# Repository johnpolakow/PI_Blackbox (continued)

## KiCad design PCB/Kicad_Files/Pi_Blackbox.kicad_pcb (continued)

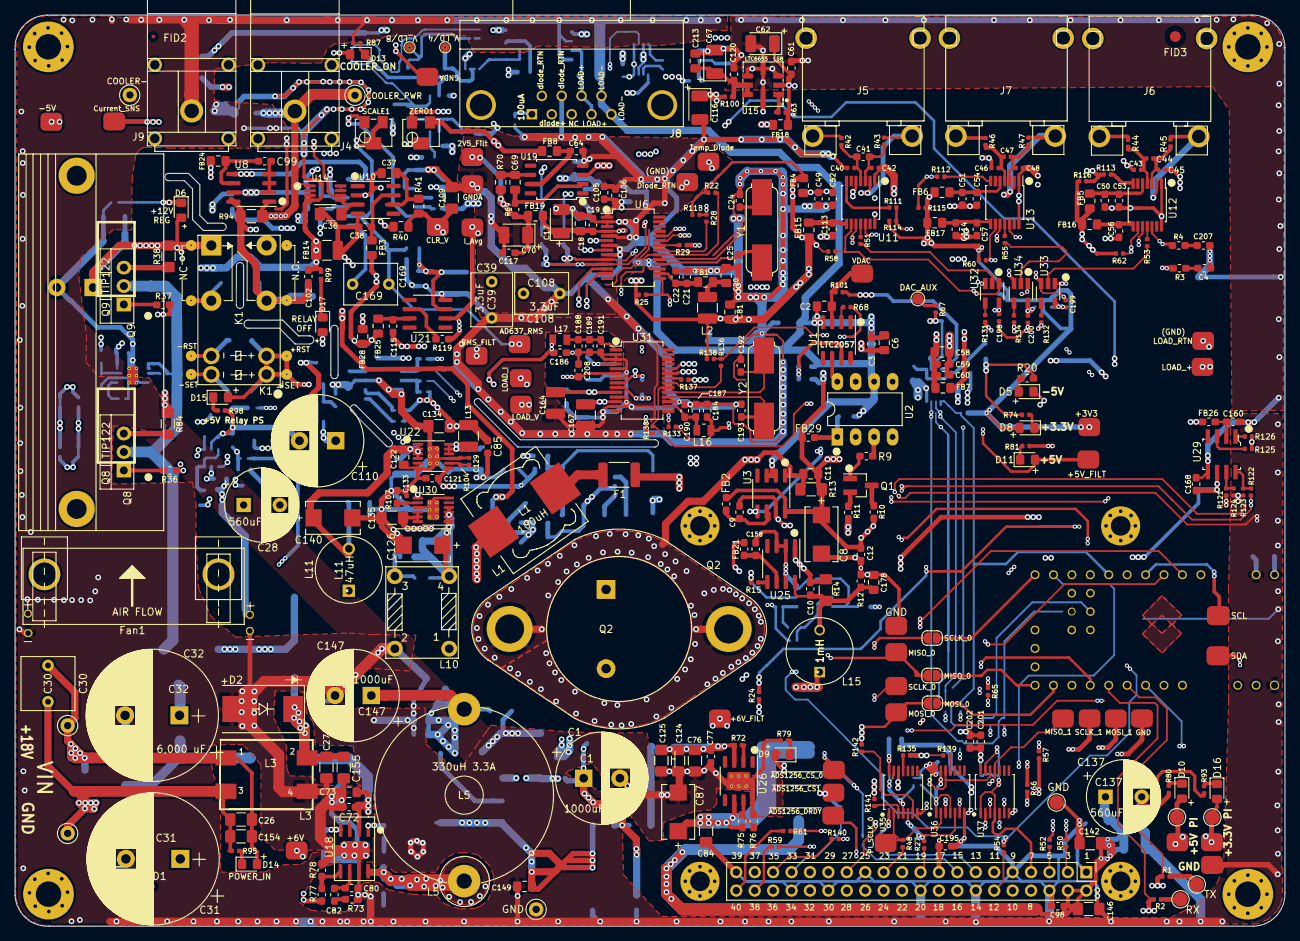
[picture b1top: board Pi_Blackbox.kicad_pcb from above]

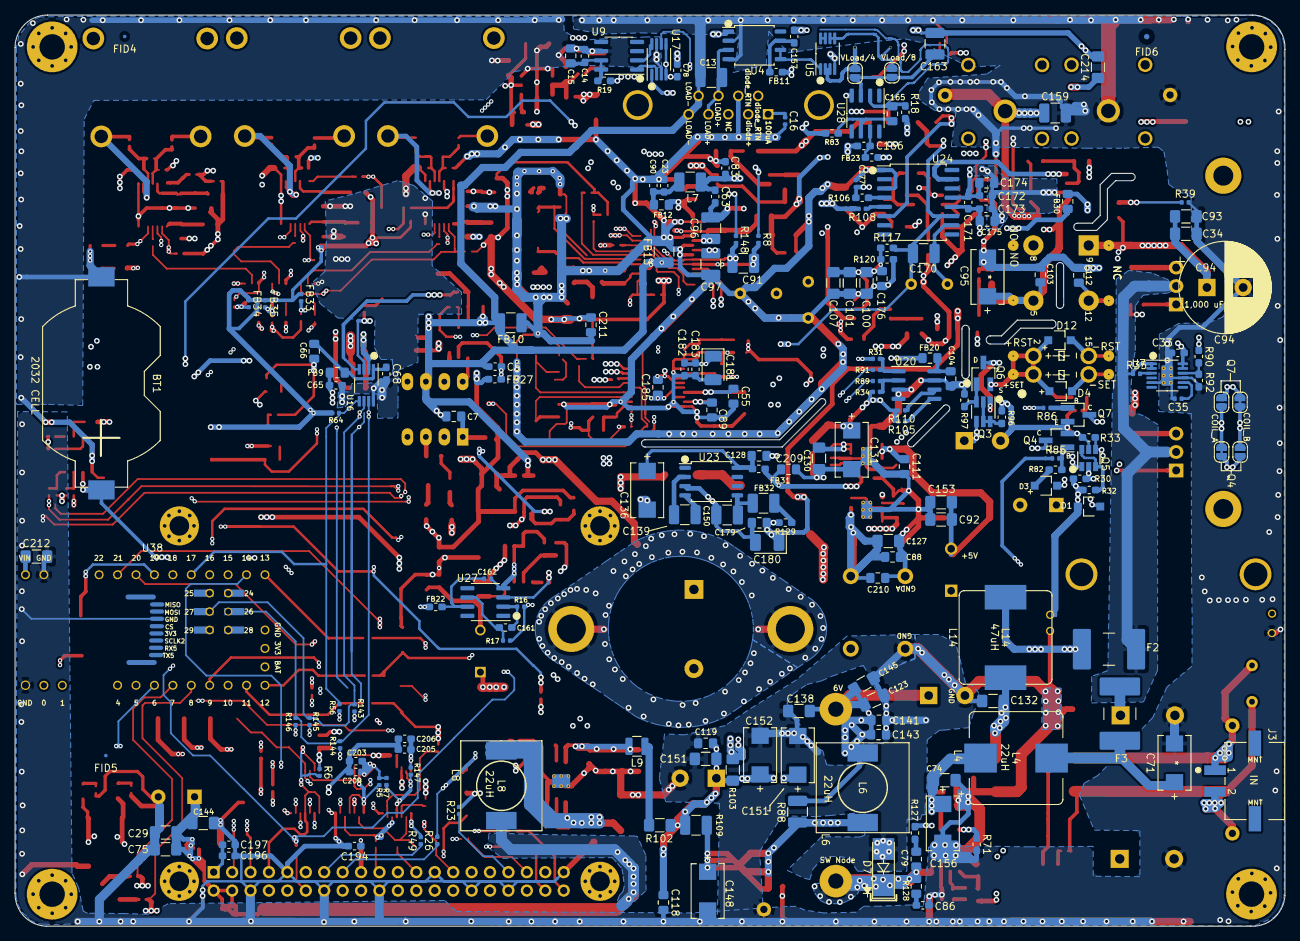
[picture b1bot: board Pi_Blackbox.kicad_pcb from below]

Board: 6 copper layers, 175.1 x 125.6 mm, 569 parts (201 on the bottom side), 276 nets.

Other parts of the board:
C151#2: 4.7uF; C_1206_3216Metric_Pad1.42x1.75mm_HandSolder
C212: 10uF; C_1206_3216Metric_Pad1.42x1.75mm_HandSolder
JP5: MOSI_0; SolderJumper-2_P1.3mm_Open_RoundedPad1.0x1.5mm
JP6: MISO_0; SolderJumper-2_P1.3mm_Open_RoundedPad1.0x1.5mm
JP7: SCLK_0; SolderJumper-2_P1.3mm_Open_RoundedPad1.0x1.5mm
U38: Teensy4.0_min_pads; Teensy40_most_pads_small_holes

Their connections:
+6V: C151#2.1; also elsewhere on the board
ADS1256_MISO: JP6.1; also elsewhere on the board
ADS1256_MOSI: JP5.1; also elsewhere on the board
ADS1256_SCLK: JP7.1; also elsewhere on the board
DAC8552_CS: U38.17; also elsewhere on the board
DAC_MOSI: U38.26; also elsewhere on the board
DAC_SCLK: U38.27; also elsewhere on the board
GND: C151#2.2, C212.2, U38.GND; also elsewhere on the board
MAX31856_CS_1: U38.4; also elsewhere on the board
MAX31856_CS_2: U38.5; also elsewhere on the board
MAX31856_CS_3: U38.20; also elsewhere on the board
MAX31856_DRDY_1: U38.21; also elsewhere on the board
MAX31856_DRDY_2: U38.28; also elsewhere on the board
MAX31856_DRDY_3: U38.29; also elsewhere on the board
MAX31856_MISO: U38.1; also elsewhere on the board
unnamed: JP5.2, U38.11
unnamed: JP6.2, U38.12
unnamed: JP7.2, U38.13
PI_+5V: C212.1, U38.VIN; also elsewhere on the board
PI_SCL: U38.19; also elsewhere on the board
PI_SDA: U38.18; also elsewhere on the board
PI_UART_RX: U38.8; also elsewhere on the board
PI_UART_TX: U38.7; also elsewhere on the board
VBat: U38.VBAT; also elsewhere on the board
~ADS1256_CS_0: U38.10; also elsewhere on the board
~ADS1256_CS_1: U38.0; also elsewhere on the board
~ADS1256_RESET: U38.22; also elsewhere on the board
~ADS1265_DRDY: U38.6; also elsewhere on the board
~ADS1265_DRDY2: U38.9; also elsewhere on the board
~BUF_EN_0: U38.14; also elsewhere on the board
~BUF_EN_1: U38.15; also elsewhere on the board
~BUF_EN_2: U38.16; also elsewhere on the board

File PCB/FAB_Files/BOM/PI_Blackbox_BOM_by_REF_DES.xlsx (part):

| Ref | Value | Description | Footprint | MFR | MFR PN | Digikey PN | Price EA
 | C2 | 1uF | 1uF, 50V, X7R | 0805 | AVX |  | 478-7956-1-ND | 0.35
 | C3 | .1uF | 50V Ceramic Capacitor X7R 0603 | 0603 | Samsung |  | 1276-1000-1-ND | 0.1
 | C5 | .1uF | 50V Ceramic Capacitor X7R 0603 | 0603 | Samsung |  | 1276-1000-1-ND | 0.1
 | C6 | 1uF | CAP CER 1UF 25V X7R 0805 | 0805 |  |  | 399-8004-1-ND | 0.15
 | C7 | 1uF | CAP CER 1UF 25V X7R 0805 | 0805 |  |  | 399-8004-1-ND | 0.15
 | C8 | 47uF | CAP TANT 47UF 10% 35V 2917 T495X | T495X476K035ATE300 | Kemet |  | 399-3905-1-ND | 2.41
 | C9 | .1uF | 50V Ceramic Capacitor X7R 0603 | 0603 | Samsung |  | 1276-1000-1-ND | 0.1
 | C10 | .1uF | 50V Ceramic Capacitor X7R 0603 | 0603 | Samsung |  | 1276-1000-1-ND | 0.1
 | C11 | .1uF | 50V Ceramic Capacitor X7R 0603 | 0603 | Samsung |  | 1276-1000-1-ND | 0.1
 | C12 | .1uF | 50V Ceramic Capacitor X7R 0603 | 0603 | Samsung |  | 1276-1000-1-ND | 0.1
 | C13 | 1uF | 1uF Film 16VDC | 1210 |  |  | 338-2778-1-ND | 0.94
 | C14 | .1uF | 50V Ceramic Capacitor X7R 0603 | 0603 | Samsung |  | 1276-1000-1-ND | 0.1
 | C15 | 1uF | CAP CER 1UF 25V X7R 0805 | 0805 |  |  | 399-8004-1-ND | 0.15
 | C16 | 1000pF | CAP CER 1000PF 16V X7R 0402 | 0402 | Kemet |  | 399-1032-1-ND | 0.1
 | C17 | 4.7uF | CAP TANT 4.7UF 10% 35V 1411 | Tantalum_3528-21_Kemet-B_Pad | Kemet |  | 399-10431-1-ND | 0.95
 | C18 | 1uF | CAP CER 1UF 25V X7R 0805 | 0805 |  |  | 399-8004-1-ND | 0.15
 | C19 | .1uF | 50V Ceramic Capacitor X7R 0603 | 0603 | Samsung |  | 1276-1000-1-ND | 0.1
 | C20 | 1uF | CAP CER 1UF 25V X7R 0805 | 0805 |  |  | 399-8004-1-ND | 0.15
 | C21 | .1uF | 50V Ceramic Capacitor X7R 0603 | 0603 | Samsung |  | 1276-1000-1-ND | 0.1
 | C22 | .1uF | 50V Ceramic Capacitor X7R 0603 | 0603 | Samsung |  | 1276-1000-1-ND | 0.1
 | C23 | 1uF | CAP CER 1UF 25V X7R 0603 | 0603 | Kemet |  | 399-7376-1-ND | 0.3
 | C24 | 20pF | 20pF, 50V, C0G | 0603 | Murata |  | 490-1410-1-ND | 0.1
 | C25 | 20pF | 20pF, 50V, C0G | 0603 | Murata |  | 490-1410-1-ND | 0.1
 | C26 | .1uF | CAP CER 0.1UF 50V Z5U 1206 | 1206 | Kemet | C1206C104Z5UACTU | 399-1258-1-ND | 0.19
 | C27 | .01uF | CAP CER 10000PF 50V X7R 1206 | 1206 | Yageo | CC1206KRX7R9BB103 | 311-1174-1-ND | 0.24
 | C29 | 10uF | CAP CER 10UF 50V X7R 1206 | 1206 | Samsung |  | 1276-6767-1-ND | 0.4
 | C33 | .01uF | 0603 .01UF 10% 50V X7R | 0603 | Kemet |  | 399-C0603C103K5RAC7081CT-ND | 0.11
 | C34 | 10uF | CAP CER 10UF 50V X7R 1206 | 1206 | Samsung |  | 1276-6767-1-ND | 0.4
 | C35 | 1000pF | CAP CER 1000PF 16V X7R 0402 | 0402 | Kemet |  | 399-1032-1-ND | 0.1
 | C36 | 10uF | CAP CER 10UF 50V X7R 1206 | 1206 | Samsung |  | 1276-6767-1-ND | 0.4
 | C37 | 10uF | CAP CER 10UF 16V X7R 0805 | 0805 | Samsung |  | 1276-6472-1-ND | 0.3
 | C38 | .1uF | 50V Ceramic Capacitor X7R 0603 | 0603 | Samsung |  | 1276-1000-1-ND | 0.1
 | C40 | .01uF | C0402C103M5RACTU | 0402 | Kemet |  | 399-7760-1-ND | 0.1
 | C41 | .1uF | 50V Ceramic Capacitor X7R 0603 | 0603 | Samsung |  | 1276-1000-1-ND | 0.1
 | C42 | .01uF | C0402C103M5RACTU | 0402 | Kemet |  | 399-7760-1-ND | 0.1
 | C43 | .01uF | C0402C103M5RACTU | 0402 | Kemet |  | 399-7760-1-ND | 0.1
 | C44 | .1uF | CAP CER 0.1UF 25V X7R 0402 | 0402 | Murata |  | 490-13341-1-ND | 0.1
 | C45 | .01uF | C0402C103M5RACTU | 0402 | Kemet |  | 399-7760-1-ND | 0.1
 | C46 | .01uF | C0402C103M5RACTU | 0402 | Kemet |  | 399-7760-1-ND | 0.1
 | C47 | .1uF | CAP CER 0.1UF 25V X7R 0402 | 0402 | Murata |  | 490-13341-1-ND | 0.1
 | C48 | .01uF | C0402C103M5RACTU | 0402 | Kemet |  | 399-7760-1-ND | 0.1
 | C49 | 1uF | CAP CER 1UF 25V X7R 0805 | 0805 |  |  | 399-8004-1-ND | 0.15
 | C50 | 1uF | CAP CER 1UF 25V X7R 0805 | 0805 |  |  | 399-8004-1-ND | 0.15
 | C51 | 1uF | CAP CER 1UF 25V X7R 0805 | 0805 |  |  | 399-8004-1-ND | 0.15
 | C52 | .1uF | 50V Ceramic Capacitor X7R 0603 | 0603 | Samsung |  | 1276-1000-1-ND | 0.1
 | C53 | .1uF | 50V Ceramic Capacitor X7R 0603 | 0603 | Samsung |  | 1276-1000-1-ND | 0.1
 | C54 | .1uF | 50V Ceramic Capacitor X7R 0603 | 0603 | Samsung |  | 1276-1000-1-ND | 0.1
 | C55 | 1uF | CAP CER 1UF 25V X7R 0805 | 0805 |  |  | 399-8004-1-ND | 0.15
 | C56 | .1uF | 50V Ceramic Capacitor X7R 0603 | 0603 | Samsung |  | 1276-1000-1-ND | 0.1
 | C57 | .1uF | 50V Ceramic Capacitor X7R 0603 | 0603 | Samsung |  | 1276-1000-1-ND | 0.1
 | C58 | 1uF | CAP CER 1UF 25V X7R 0805 | 0805 |  |  | 399-8004-1-ND | 0.15
 | C59 | .1uF | 50V Ceramic Capacitor X7R 0603 | 0603 | Samsung |  | 1276-1000-1-ND | 0.1
 | C60 | .01uF | 0603 .01UF 10% 50V X7R | 0603 | Kemet |  | 399-C0603C103K5RAC7081CT-ND | 0.11
 | C61 | .1uF | 50V Ceramic Capacitor X7R 0603 | 0603 | Samsung |  | 1276-1000-1-ND | 0.1
 | C62 | 4.7uF | CAP TANT 4.7UF 10% 35V 1411 | Tantalum_EIA-3528-21_Kemet-B_Pad | Kemet |  | 399-10431-1-ND | 0.95
 | C63 | .01uF | 0603 .01UF 10% 50V X7R | 0603 | Kemet |  | 399-C0603C103K5RAC7081CT-ND | 0.11
 | C64 | .1uF | 50V Ceramic Capacitor X7R 0603 | 0603 | Samsung |  | 1276-1000-1-ND | 0.1
 | C65 | .01uF | 0603 .01UF 10% 50V X7R | 0603 | Kemet |  | 399-C0603C103K5RAC7081CT-ND | 0.11
 | C66 | 1uF | CAP CER 1UF 25V X7R 0805 | 0805 |  |  | 399-8004-1-ND | 0.15
 | C67 | 4.7uF | CAP TANT 4.7UF 10% 35V 1411 | Tantalum_EIA-3528-21_Kemet-B_Pad | Kemet |  | 399-10431-1-ND | 0.95
 | C68 | .1uF | 50V Ceramic Capacitor X7R 0603 | 0603 | Samsung |  | 1276-1000-1-ND | 0.1
 | C69 | 1uF | CAP CER 1UF 25V X7R 0805 | 0805 |  |  | 399-8004-1-ND | 0.15
 | C70 | 4.7uF | CAP TANT 4.7UF 10% 35V 1411 | Tantalum_EIA-3528-21_Kemet-B_Pad | Kemet |  | 399-10431-1-ND | 0.95
 | C71 | 47uF | CAP TANT 47UF 10% 35V 2917 T495X | T495X476K035ATE300 | Kemet |  | 399-3905-1-ND | 2.41
 | C72 | .1uF | 50V Ceramic Capacitor X7R 0603 | 0603 | Samsung |  | 1276-1000-1-ND | 0.1
 | C73 | 1uF | CAP CER 1UF 25V X7R 0805 | 0805 |  |  | 399-8004-1-ND | 0.15
 | C74 | 10uF | CAP CER 10UF 50V X7R 1206 | 1206 | Samsung |  | 1276-6767-1-ND | 0.4
 | C75 | 10uF | CAP CER 10UF 50V X7R 1206 | 1206 | Samsung |  | 1276-6767-1-ND | 0.4
 | C76 | 10uF | CAP CER 10UF 50V X7R 1206 | 1206 | Samsung |  | 1276-6767-1-ND | 0.4
 | C77 | .1uF | 50V Ceramic Capacitor X7R 0603 | 0603 | Samsung |  | 1276-1000-1-ND | 0.1
 | C78 | .1uF | 50V Ceramic Capacitor X7R 0603 | 0603 | Samsung |  | 1276-1000-1-ND | 0.1
 | C79 | .1uF | CAP CER 0.1UF 25V X7R 0805 | 0805 | Kemet | C0805C104M3RACTU | 399-8000-1-ND | 0.1
 | C80 | 12pF | CAP CER 12PF 50V C0G/NP0 0603 | 0603 | Kemet | C0603C120J5GACTU | 399-1050-1-ND | 0.1
 | C81 | 1uF | CAP CER 1UF 25V X7R 0805 | 0805 |  |  | 399-8004-1-ND | 0.15
 | C82 | 3nF | CAP CER 3000PF 50V C0G/NP0 0603 | 0603 | Murata | GRM1885C1H302JA01D | 490-6384-1-ND | 0.19
 | C83 | .1uF | 50V Ceramic Capacitor X7R 0603 | 0603 | Samsung |  | 1276-1000-1-ND | 0.1
 | C84 | 10uF | CAP CER 10UF 50V X7R 1206 | 1206 | Samsung |  | 1276-6767-1-ND | 0.4
 | C85 | .1uF | 50V Ceramic Capacitor X7R 0603 | 0603 | Samsung |  | 1276-1000-1-ND | 0.1
 | C86 | 680pF | CAP CER 680PF 250V C0G/NP0 0603 | 0603 | Kemet | C0603C681JAGAC7867 | 399-14994-1-ND | 0.11
 | C87 | 47uF | CAP TANT 47UF 10% 35V 2917 T495X | T495X476K035ATE300 | Kemet |  | 399-3905-1-ND | 2.41
 | C88 | 1uF | CAP CER 1UF 25V X7R 0805 | 0805 |  |  | 399-8004-1-ND | 0.15
 | C89 | 1uF | CAP CER 1UF 25V X7R 0805 | 0805 |  |  | 399-8004-1-ND | 0.15
 | C90 | .1uF | 50V Ceramic Capacitor X7R 0603 | 0603 | Samsung |  | 1276-1000-1-ND | 0.1
 | C91 | 1uF | 1uF Film 16VDC | 1210 |  |  | 338-2778-1-ND | 0.94
 | C92 | 10uF | CAP CER 10UF 50V X7R 1206 | 1206 | Samsung |  | 1276-6767-1-ND | 0.4
 | C93 | 10uF | CAP CER 10UF 50V X7R 1206 | 1206 | Samsung |  | 1276-6767-1-ND | 0.4
 | C95 | 47uF | CAP TANT 47UF 10% 35V 2917 T495X | T495X476K035ATE300 | Kemet |  | 399-3905-1-ND | 2.41
 | C96 | 1uF | 1uF Film 16VDC | 1210 |  |  | 338-2778-1-ND | 0.94
 | C97 | 1uF | 1uF Film 16VDC | 1210 |  |  | 338-2778-1-ND | 0.94
 | C98 | 1uF | CAP CER 1UF 25V X7R 0603 | 0603 | Kemet |  | 399-7376-1-ND | 0.3
 | C99 | .1uF | 50V Ceramic Capacitor X7R 0603 | 0603 | Samsung |  | 1276-1000-1-ND | 0.1
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
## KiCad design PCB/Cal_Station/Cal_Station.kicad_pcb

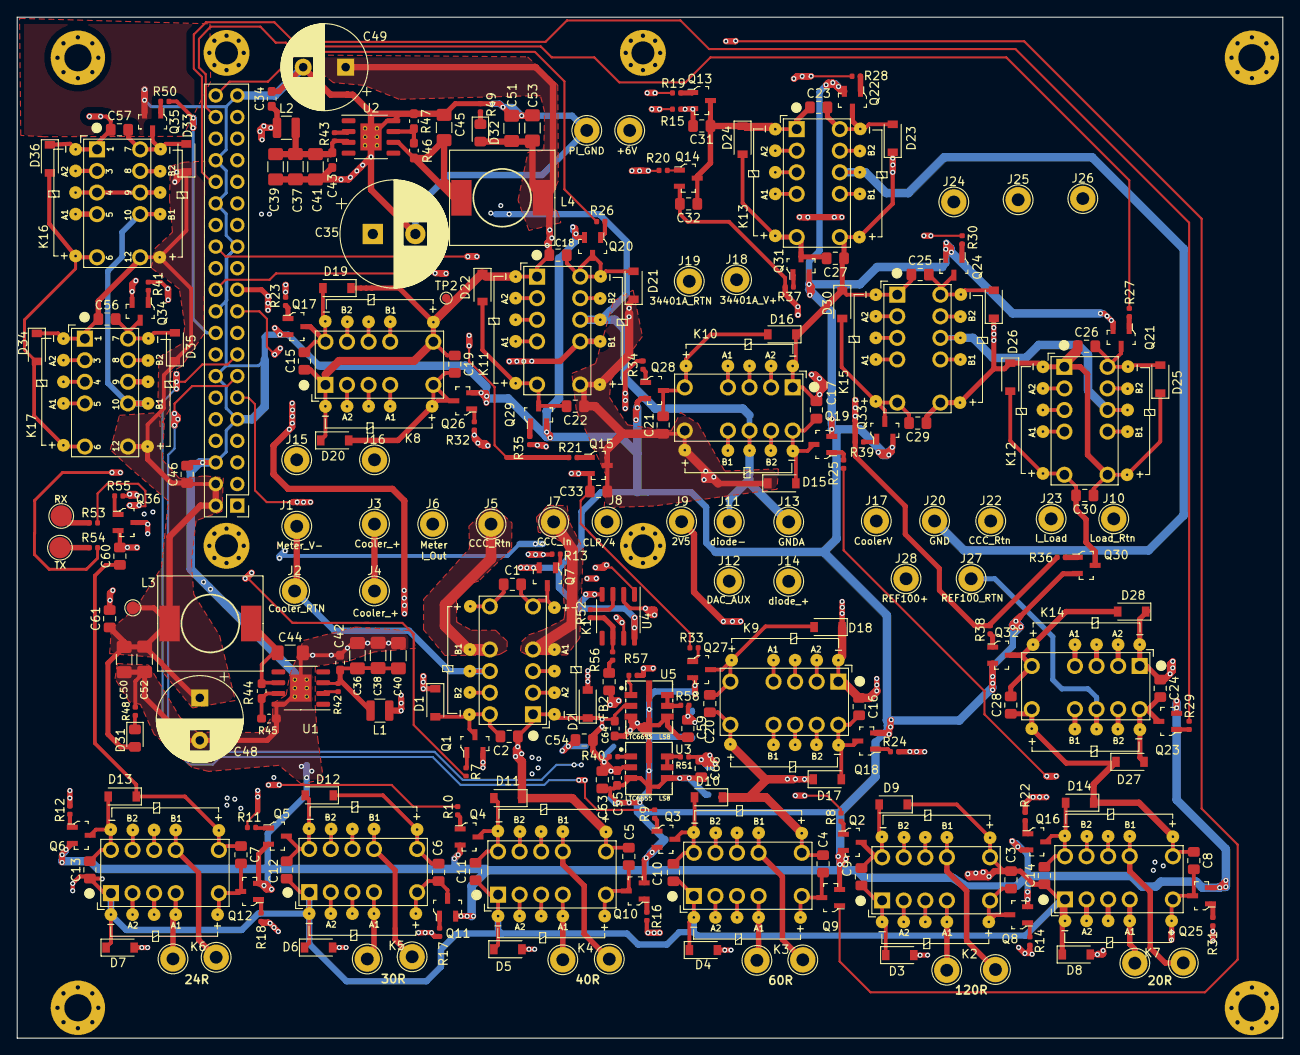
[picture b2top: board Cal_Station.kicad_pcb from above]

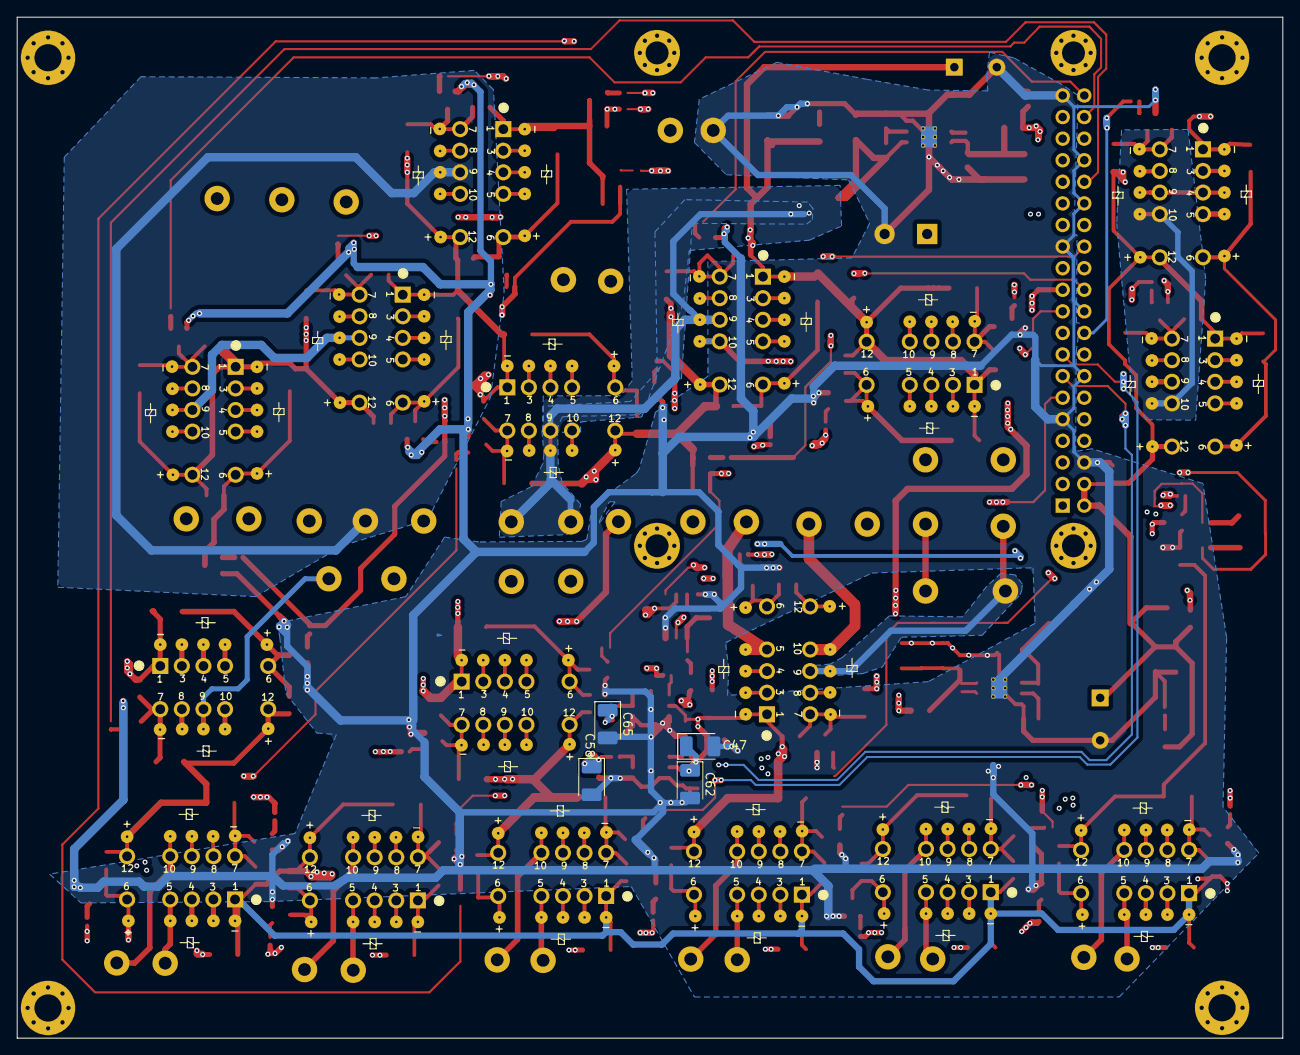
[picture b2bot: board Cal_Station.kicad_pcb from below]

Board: 4 copper layers, 148.9 x 120.1 mm, 271 parts (4 on the bottom side), 160 nets.

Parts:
C1, C2, C3, C4, C5, C6, C7, C8, C9, C10, C11, C12, C13, C14, C15, C16, C17, C18, C19, C20, C21, C22, C23, C24, C25, C26, C27, C28, C29, C30, C31, C32, C33, C46, C54, C56, C57, C59, C61, C63, C66: 10uF; C_0805_2012Metric_Pad1.15x1.40mm_HandSolder
C34: 1uF; C_0603_1608Metric_Pad1.05x0.95mm_HandSolder
C35: 1000uF; CP_Radial_D12.5mm_P5.00mm
C36, C37, C38, C39, C40, C41, C44, C45, C50, C51, C52, C53: 10uF; C_1206_3216Metric_Pad1.42x1.75mm_HandSolder
C42, C43, C55, C64: .1uF; C_0603_1608Metric_Pad1.05x0.95mm_HandSolder
C47, C58, C62, C65: 4.7uF; CP_EIA-3528-21_Kemet-B_Pad1.50x2.35mm_HandSolder
C48, C49: 560uF; CP_Radial_D10.0mm_P5.00mm
C60: 1uF; C_0805_2012Metric_Pad1.15x1.40mm_HandSolder
D1, D2, D3, D4, D5, D6, D7, D8, D9, D10, D11, D12, D13, D14, D15, D16, D17, D18, D19, D20, D21, D22, D23, D24, D25, D26, D27, D28, D29, D30, D33, D34, D35, D36: 1N4148W; D_SOD-123
D31, D32: LED GRN; LED_0805_2012Metric_Pad1.15x1.40mm_HandSolder
FB2: Ferrite_Bead_Small; L_0805_2012Metric_Pad1.15x1.40mm_HandSolder
H1, H2, H3, H4: MountingHole; MountingHole_2.7mm_M2.5_Pad_Via
H5, H6, H7, H8: MountingHole; MountingHole_3.2mm_M3_Pad_Via
J1: Meter_V-; TestPoint_THTPad_D3.0mm_Drill1.5mm
J2: Cool_Pwr_RTN; TestPoint_THTPad_D3.0mm_Drill1.5mm
J3, J4: Cool_PWR_+; TestPoint_THTPad_D3.0mm_Drill1.5mm
J5: CCC_RTN; TestPoint_THTPad_D3.0mm_Drill1.5mm
J6: Meter_OUT; TestPoint_THTPad_D3.0mm_Drill1.5mm
J7: CCC_IN; TestPoint_THTPad_D3.0mm_Drill1.5mm
J8: CoolerV/4; TestPoint_THTPad_D3.0mm_Drill1.5mm
J9: 2V5_Filt; TestPoint_THTPad_D3.0mm_Drill1.5mm
J10: ILoad_RTN; TestPoint_THTPad_D3.0mm_Drill1.5mm
J11: GNDA; TestPoint_THTPad_D3.0mm_Drill1.5mm
J12: DAC_AUX; TestPoint_THTPad_D3.0mm_Drill1.5mm
J13: Diode_SNS-; TestPoint_THTPad_D3.0mm_Drill1.5mm
J14: Diode_SNS_+; TestPoint_THTPad_D3.0mm_Drill1.5mm
J15: VLoad+; TestPoint_THTPad_D3.0mm_Drill1.5mm
J16: VLoad_RTN; TestPoint_THTPad_D3.0mm_Drill1.5mm
J17: CoolerV; TestPoint_THTPad_D3.0mm_Drill1.5mm
J18, J24: VIN; TestPoint_THTPad_D3.0mm_Drill1.5mm
J19, J25: RTN; TestPoint_THTPad_D3.0mm_Drill1.5mm
J20: GND; TestPoint_THTPad_D3.0mm_Drill1.5mm
J22: VLoad/8; TestPoint_THTPad_D3.0mm_Drill1.5mm
J23: ILoad; TestPoint_THTPad_D3.0mm_Drill1.5mm
J26: AMP_IN; TestPoint_THTPad_D3.0mm_Drill1.5mm
J27: REF100_RTN; TestPoint_THTPad_D3.0mm_Drill1.5mm
J28: REF100+; TestPoint_THTPad_D3.0mm_Drill1.5mm
K1, K2, K3, K4, K5, K6, K7: 2A Relay; Panasonic_TX2_2
K8, K9, K10, K11, K12, K13, K14, K15, K16, K17: TXS2; Panasonic_TX2_2
L1, L2: 10uH; 10uH_Wurth_74479887310A
L3, L4: 22uH; Sumida_CDRH105
PI1: RPI_3B+_Header; PinHeader_2x20_P2.54mm_Vertical
Q1, Q2, Q3, Q4, Q5, Q6, Q7, Q8, Q9, Q10, Q11, Q12, Q13, Q14, Q15, Q16, Q17, Q18, Q19, Q20, Q21, Q22, Q23, Q24, Q25, Q26, Q27, Q28, Q29, Q30, Q31, Q32, Q33, Q34, Q35, Q36: MMBT2222A; SOT-23-3
R7, R8, R9, R10, R11, R12, R13, R14, R15, R16, R17, R18, R22, R23, R24, R25, R26, R27, R28, R29, R30, R31, R32, R33, R34, R35, R36, R37, R38, R39, R41, R50: 300R; C_0402_1005Metric
R19, R20, R21, R52, R55: 100R; C_0402_1005Metric
R40, R57: 1k; C_0402_1005Metric
R42, R43: 1K; R_0402_1005Metric
R44, R46: 20k; R_0603_1608Metric_Pad1.05x0.95mm_HandSolder
R45, R47: 2.2k; R_0603_1608Metric_Pad1.05x0.95mm_HandSolder
R48, R49: 500R; R_0402_1005Metric
R51, R53, R54, R56, R58: 50R; C_0402_1005Metric
TP1: PI_+5V; TestPoint_Pad_D1.5mm
TP2: +5V; TestPoint_Pad_D1.0mm
TP3, TP4, TP5, TP6, TP7, TP8, TP9, TP10, TP11, TP12, TP13, TP14: TestPoint_Small; TestPoint_THTPad_D3.0mm_Drill1.5mm
TP15: RX; TestPoint_Pad_D2.5mm
TP16: TX; TestPoint_Pad_D2.5mm
TP17: GND; TestPoint_THTPad_D3.0mm_Drill1.5mm
TP18: +6V; TestPoint_THTPad_D3.0mm_Drill1.5mm
U1, U2: TPS7A7002; SOIC-8-1EP_3.9x4.9mm_P1.27mm_EP2.514x3.2mm_ThermalVias
U3, U5: LTC6655; LTC6655_LS8
U4: LTC2057; SO-8_3.9x4.9mm_P1.27mm

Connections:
+5V: C1.1, C2.1, C3.1, C4.1, C5.1, C6.1, C7.1, C8.1, C9.1, C10.1, C11.1, C12.1, C13.1, C14.1, C15.1, C16.1, C17.1, C18.1, C19.1, C20.1, C21.1, C22.1, C23.1, C24.1, C25.1, C26.1, C27.1, C28.1, C29.1, C30.1, C31.1, C32.1, C33.1, C47.1, C49.1, C51.1, C53.1, C54.1, C55.1, C60.1, C62.1, C63.1, C64.1, D1.1, D2.1, D3.1, D4.1, D5.1, D6.1, D7.1, D8.1, D9.1, D10.1, D11.1, D12.1, D13.1, D14.1, D15.1, D16.1, D17.1, D18.1, D19.1, D20.1, D21.1, D22.1, D23.1, D24.1, D25.1, D26.1, D27.1, D28.1, D29.1, D30.1, D32.2, K1.1, K1.12, K2.1, K2.12, K3.1, K3.12, K4.1, K4.12, K5.1, K5.12, K6.1, K6.12, K7.1, K7.12, K8.1, K8.12, K9.1, K9.12, K10.1, K10.12, K11.1, K11.12, K12.1, K12.12, K13.1, K13.12, K14.1, K14.12, K15.1, K15.12, L4.2, Q13.3, Q14.3, Q15.3, R40.1, R57.1, TP2.1, U3.2, U4.7, U5.2
+6V: C34.1, C35.1, L1.1, L2.1, TP18.1
/34401_A/2V5_filt: J9.1, K9.4
/34401_A/34401A_RTN: J19.1, K8.10, K9.10, K10.10, K11.10
/34401_A/34401A_V+: J18.1, K8.5, K9.5, K10.5, K11.5
/34401_A/COOLERV_div4: J8.1, K11.4
/34401_A/GNDA: J11.1, J13.1, K9.9, K10.9, K11.9, K16.10, K17.10
/34401_A/LOAD+: J15.1, K8.4
/34401_A/LOAD_RTN: J16.1, K8.9
/34401_B/34401B_I+: J26.1, K12.5, K14.5
/34401_B/34401B_RTN: J25.1, K12.10, K13.10, K14.10, K15.10
/34401_B/34401B_V+: J24.1, K13.5, K15.5
/34401_B/CoolerV: J17.1, K13.4
/34401_B/GND: J20.1, K13.9
/34401_B/I_LOAD: J23.1, K12.4
/34401_B/LOAD_RTN: J10.1, K12.9, K15.9
/34401_B/REF100+: J28.1, K14.4
/34401_B/REF100_RTN: J27.1, K14.9
/34401_B/VLoad_div8: J22.1, K15.4
/PI_Power_Supply/+5V_unfilt: C45.1, L4.1, R46.1, U2.6
/PI_Power_Supply/PI_PS: C44.1, L3.1, R44.1, U1.6
/PWR_IN: J6.1, K1.4
/PWR_RTN: J1.1, J2.1, K1.9
/Resistor_Array/RES_IN: K1.3, K2.9, K3.9, K4.9, K5.9, K6.9, K7.9
/Resistor_Array/RES_RTN: K1.8, K2.4, K3.4, K4.4, K5.4, K6.4, K7.4
BANK_A_RESET: C33.2, Q15.2, R32.2, R33.2, R34.2, R35.2
BANK_A_RESET_SIGNL: PI1.24, R21.2
BANK_B_RESET: C32.2, Q14.2, R36.2, R37.2, R38.2, R39.2
BANK_B_RESET_SIGNL: PI1.22, R20.2
CAL_RESET: C61.2, D34.2, D36.2, K16.6, K17.6, Q36.3
CAL_RESET_SIGNL: PI1.12, R55.2
DAC_AUX: J12.1, U4.2
DAC_AUX_BUF: FB2.1, J14.1, K10.4, K16.5, K17.5
K1_RESET: C1.2, D2.2, K1.6, Q7.3
K1_RESET_SIGNL: PI1.11, R13.2
K1_SET: C2.2, D1.2, K1.7, Q1.3
K1_SET_SGNL: PI1.7, R7.2
K2_RESET: C3.2, D3.2, K2.6, Q8.3
K2_RESET_SIGNL: C31.2, Q13.2, R14.2, R15.2, R16.2, R17.2, R18.2, R31.2
K2_SET: C9.2, D9.2, K2.7, Q2.3
K2_SET_SIGNL: PI1.13, R8.2
K3_RESET: C4.2, D4.2, K3.6, Q9.3
K3_SET: C10.2, D10.2, K3.7, Q3.3
K3_SET_SIGNL: PI1.15, R9.2
K4_RESET: C5.2, D5.2, K4.6, Q10.3
K4_SET: C11.2, D11.2, K4.7, Q4.3
K4_SET_SIGNL: PI1.19, R10.2
K5_RESET: C6.2, D6.2, K5.6, Q11.3
K5_SET: C12.2, D12.2, K5.7, Q5.3
K5_SET_SIGNL: PI1.21, R11.2
K6_RESET: C7.2, D7.2, K6.6, Q12.3
K6_SET: C13.2, D13.2, K6.7, Q6.3
K6_SET_SIGNL: PI1.23, R12.2
K7_RESET: C8.2, D8.2, K7.6, Q25.3
K7_SET: C14.2, D14.2, K7.7, Q16.3
K7_SET_SIGNL: PI1.29, R22.2
K8_RESET: C19.2, D20.2, K8.6, Q26.3
K8_SET: C15.2, D19.2, K8.7, Q17.3
K8_SET_SIGNL: PI1.33, R23.2
K9_RESET: C20.2, D18.2, K9.6, Q27.3
K9_SET: C16.2, D17.2, K9.7, Q18.3
K9_SET_SIGNL: PI1.35, R24.2
K10_RESET: C21.2, D16.2, K10.6, Q28.3
K10_SET: C17.2, D15.2, K10.7, Q19.3
K10_SET_SIGNL: PI1.37, R25.2
K11_RESET: C22.2, D22.2, K11.6, Q29.3
K11_SET: C18.2, D21.2, K11.7, Q20.3
K11_SET_SIGNL: PI1.40, R26.2
K12_RESET: C30.2, D26.2, K12.6, Q30.3
K12_SET: C26.2, D25.2, K12.7, Q21.3
K12_SET_SIGNL: PI1.38, R27.2
K13_RESET: C27.2, D24.2, K13.6, Q31.3
K13_SET: C23.2, D23.2, K13.7, Q22.3
K13_SET_SIGNL: PI1.36, R28.2
K14_RESET: C28.2, D28.2, K14.6, Q32.3
K14_SET: C24.2, D27.2, K14.7, Q23.3
K14_SET_SIGNL: PI1.32, R29.2
K15_RESET: C29.2, D30.2, K15.6, Q33.3
K15_SET: C25.2, D29.2, K15.7, Q24.3
K15_SET_SIGNL: PI1.26, R30.2
K16_SET: C57.2, D33.2, K16.7, Q35.3
K16_SET_SIGNL: PI1.18, R50.2
K17_SET: C56.2, D35.2, K17.7, Q34.3
K17_SET_SIGNL: PI1.16, R41.2
LTC2057_SHDN: PI1.3, U4.1
unnamed: C36.1, C38.1, C40.1, C42.1, L1.2, R42.2, U1.3
unnamed: C37.1, C39.1, C41.1, C43.1, L2.2, R43.2, U2.3
unnamed: D31.1, R48.1
unnamed: D32.1, R49.1
unnamed: FB2.2, R56.1
unnamed: J3.1, J4.1
unnamed: J5.1, K1.10
unnamed: J7.1, K1.5
unnamed: K2.5, TP12.1
unnamed: K2.10, TP11.1
unnamed: K3.5, TP14.1
unnamed: K3.10, TP13.1
unnamed: K4.5, TP4.1
unnamed: K4.10, TP3.1
unnamed: K5.5, TP6.1
unnamed: K5.10, TP5.1
unnamed: K6.5, TP8.1
unnamed: K6.10, TP7.1
unnamed: K7.5, TP10.1
unnamed: K7.10, TP9.1
unnamed: K16.4, K16.9
unnamed: Q1.1, R7.1
unnamed: Q2.1, R8.1
unnamed: Q3.1, R9.1
unnamed: Q4.1, R10.1
unnamed: Q5.1, R11.1
unnamed: Q6.1, R12.1
unnamed: Q7.1, R13.1
unnamed: Q8.1, R14.1
unnamed: Q9.1, R15.1
unnamed: Q10.1, R16.1
unnamed: Q11.1, R17.1
unnamed: Q12.1, R18.1
unnamed: Q13.1, R19.1
unnamed: Q14.1, R20.1
unnamed: Q15.1, R21.1
unnamed: Q16.1, R22.1
unnamed: Q17.1, R23.1
unnamed: Q18.1, R24.1
unnamed: Q19.1, R25.1
unnamed: Q20.1, R26.1
unnamed: Q21.1, R27.1
unnamed: Q22.1, R28.1
unnamed: Q23.1, R29.1
unnamed: Q24.1, R30.1
unnamed: Q25.1, R31.1
unnamed: Q26.1, R32.1
unnamed: Q27.1, R33.1
unnamed: Q28.1, R34.1
unnamed: Q29.1, R35.1
unnamed: Q30.1, R36.1
unnamed: Q31.1, R37.1
unnamed: Q32.1, R38.1
unnamed: Q33.1, R39.1
unnamed: Q34.1, R41.1
unnamed: Q35.1, R50.1
unnamed: Q36.1, R55.1
unnamed: R40.2, U3.1
unnamed: R42.1, U1.2
unnamed: R43.1, U2.2
unnamed: R44.2, R45.1, U1.7
unnamed: R46.2, R47.1, U2.7
unnamed: R51.2, U3.6, U3.7
unnamed: R52.1, R56.2, U4.6
unnamed: R52.2, U4.3
unnamed: R53.1, TP15.1
unnamed: R54.1, TP16.1
unnamed: R57.2, U5.1
unnamed: R58.2, U5.6, U5.7
PI_+5V: C46.1, C48.1, C50.1, C52.1, C56.1, C57.1, C61.1, D31.2, D33.1, D34.1, D35.1, D36.1, K16.1, K16.12, K17.1, K17.12, L3.2, PI1.2, PI1.4, TP1.1
PI_GND: C34.2, C35.2, C36.2, C37.2, C38.2, C39.2, C40.2, C41.2, C42.2, C43.2, C44.2, C45.2, C46.2, C47.2, C48.2, C49.2, C50.2, C51.2, C52.2, C53.2, C54.2, C55.2, C58.2, C59.2, C60.2, C62.2, C63.2, C64.2, C65.2, C66.2, K17.9, PI1.6, PI1.9, PI1.14, PI1.20, PI1.25, PI1.30, PI1.34, PI1.39, Q1.2, Q2.2, Q3.2, Q4.2, Q5.2, Q6.2, Q7.2, Q8.2, Q9.2, Q10.2, Q11.2, Q12.2, Q16.2, Q17.2, Q18.2, Q19.2, Q20.2, Q21.2, Q22.2, Q23.2, Q24.2, Q25.2, Q26.2, Q27.2, Q28.2, Q29.2, Q30.2, Q31.2, Q32.2, Q33.2, Q34.2, Q35.2, Q36.2, R45.2, R47.2, R48.2, R49.2, TP17.1, U1.8, U1.9, U2.8, U2.9, U3.3, U3.4, U3.5, U3.8, U4.4, U4.8, U5.3, U5.4, U5.5, U5.8
RES_ARRAY_RESET_SIGNL: PI1.31, R19.2
RX: PI1.10, R53.2
TX: PI1.8, R54.2
Vref_OUT: C58.1, C59.1, C65.1, C66.1, K17.4, R51.1, R58.1

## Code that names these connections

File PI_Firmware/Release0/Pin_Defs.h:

#ifndef PIN_DEFINITIONS
#define PIN_DEFINITIONS

// Pin Numbering
/*
Rasperry Pi Physical Pin Numbering w/ bcm2835 library pin Numbering
            BCM2835           Raspberry Pi
Function     pin#             physical pin#
SDA1          2                   3       PI_SDA
SCL1          3                   5       PI_SCL
GPCLK0        4                   7       BUF_EN_2
GPCLK1        5                   29      MAX31856_DRDY1
GPCLK2        6                   31      SW_CTRL_100uA
SPI0_CE1_N    7                   26      MAX31856_CS3
SPI0_CE0_N    8                   24      MAX31856_CS2
SPI0_MISO     9                   21      ADS1256_MISO
SPI0_MOSI     10                  19      ADS1256 MOSI
SPI0_SCLK     11                  23      ADS1256_SCLK
PWM0          12                  32      RELAY_RESET
PWM1          13                  33      ADS1256_CS_1
TXD0          14                  8       CCC_UART_TX
RXD0          15                  10      CCC_UART_RX
SPI1_CE2      16                  36      MAX31856_DRDY2
SPI1_CE1      17                  11      ADS1256_DRDY
PCM_CLK       18                  12      ADS1256_RESET
SPI1_MISO     19                  35      MISO_SPI1
SPI1_MOSI     20                  38      MOSI_SPI1
SPI1_SCLK     21                  40      SCLK_SPI1
SD0_CLK       22                  15      ADS1256_CS_0
SD0_CMD       23                  16      DAC8552_CS
SD0_DAT0      24                  18      BUF_EN_1
SD0_DAT1      25                  22      MAX31856_CS1
SD0_DAT2      26                  37      MAX31856_DRDY3
SD0_DAT3      27                  13      BUF_EN_0
              01                  28      RELAY_SET
              00                  27      ADS1256_DRDY2
*/
#define BUS_SPEED_100KHZ  100000
#define BUS_SPEED_300KHZ  300000
#define BUS_SPEED_400KHZ  400000

#define DS3231_ADDRESS    0x68

#define ADS1256_DRDY_0    17        // physical pin 11
#define ADS1256_DRDY_1     0        // physical pin 27
#define ADS1256_RESET     18        // physical pin 12

#define ADS1256_CS_0      22        // Physical pin 15
#define ADS1256_CS_1      13        // physical pin 33

//#define	DAC8552_CS	    RPI_GPIO_P1_16	// Physical pin 16
#define	DAC8552_CS	      23	      // Physical pin 16

#define MAX31856_CS_1     25        // physical pin 25
#define MAX31856_CS_2     8         // physical pin 24
#define MAX31856_CS_3     7         // physical pin 26
#define MAX31856_DRDY_1   5         // physcial pin 29
#define MAX31856_DRDY_2   16        // physical pin 36
#define MAX31856_DRDY_3   26        // physical pin 37

#define BUFFER_EN_1       24
#define BUFFER_EN_2       4         // physical pin 7
#define BUFFER_EN_0       27        // physical pin 13

#define PI_MOSI_0         10        // physical pin 19
#define PI_MISO_0         9         // physical pin 21
#define PI_SCLK_0         11        // physical pin 23

#define PI_MOSI_1         20        // physical pin 38
#define PI_MISO_1         19        // physical pin 35
#define PI_SCLK_1         21        // physical pin 40

#define RELAY_RESET       12        // physical pin 32
#define RELAY_SET         1         // physical pin 28
#define SW_CTRL_100uA     6         // physical pin 31
#define PI_UART_TX        14        // physical pin 8
#define PI_UART_RX        15        // physical pin 10






typedef struct ADS1256
{
    int CS_pin;
    int DRDY_pin;
    int RESET_pin;
		int BUF_EN_pin;
} ADC;

ADC ADC0;
ADC ADC1;

int CURRENT_SOURCE_SELECT = 0;

bool RELAY_is_ON = false;
const int NUM_MEAS_SAMPLES = 3;







#endif

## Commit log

2021-06-23 updated firmware
2021-06-29 added README
